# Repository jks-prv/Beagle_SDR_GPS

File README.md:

[updated 10 November 2024]

Click image for full size.

KiwiSDR
=======

> [!IMPORTANT]
> This repo is now archived.
> Look for future updates on the new repo named "KiwiSDR".

Software-defined Radio (SDR) and GPS for the BeagleBone
----------------------------------------------------------------------

An add-on board ("cape") that turns your BeagleBone into a web-accessible shortwave receiver.

### Details

* Listen live: [List](http://rx.kiwisdr.com), [Map](http://map.kiwisdr.com)
* [Online Store](https://kiwisdr.nz)
* [Project webpage](http://www.kiwisdr.com)
* [Operating information: installation, operation, FAQ](http://www.kiwisdr.com/info)
* [User Forum](http://forum.kiwisdr.com)
* Latest [source code commits](https://github.com/jks-prv/Beagle_SDR_GPS/commits/master)
* [Design review document](http://kiwisdr.com/docs/KiwiSDR/KiwiSDR.design.review.pdf)
* [KiwiSDR 1 Schematic](http://www.kiwisdr.com/docs/KiwiSDR/kiwi.schematic.pdf)
* [KiwiSDR 2 Schematic](http://www.kiwisdr.com/docs/KiwiSDR/kiwi-2.schematic.pdf)

### Description
This SDR is a bit different. It has a web interface that can be used by up to four separate listeners. Each one listening and tuning an independent frequency simultaneously. See the screenshots below.

### Components
* SDR covering the 10 kHz to 30 MHz (VLF-HF) spectrum.
* Web interface based on [OpenWebRX](https://github.com/ha7ilm/openwebrx) from András Retzler, HA7ILM.
* Integrated software-defined GPS receiver from Andrew Holme's [Homemade GPS Receiver](http://www.aholme.co.uk/GPS/Main.htm).
* LTC/Analog Devices 14-bit 65 MHz ADC.
* Xilinx/AMD Artix-7 A35 FPGA.
* Maxim/Analog Devices MAX2769B GPS front-end.
* Kiwi board works with BeagleBone Green, Black, BBAI or BBAI-64.

### Features
* Open Source.
* Browser-based interface allowing multiple simultaneous user web connections.
* Each connection tunes an independent receiver channel over the entire spectrum.
* Waterfall tunes independently of audio and includes zooming and panning.
* Multi-channel, parallel DDC design using bit-width optimized CIC filters.
* Built-in signal decoding: ALE CW DRM FAX FSK FT8 HFDL IBP NAVTEX/DSC SSTV TDoA WSPR and more.
* Good performance at VLF/LF since we personally spend time monitoring those frequencies.
* Automatic frequency calibration via received GPS timing.
* Easy hardware and software setup. Browser-based configuration interface.
* KiwiSDR 2 features:
    * Reverse proxy service enabled by default to ease network installation.
    * 0 - 31.5 dB electronic attenuator.
    * External ADC clock input.
    * Built-in self test for checking the RF path.
    * 5V input reverse polarity protection.

### Status

Give the live receivers a try at the links above. You'll need a recent version of a modern web browser that supports HTML5. The web interface works, with some problems, on mobile devices. But there is no mobile version of the interface yet.

A second generation device, the [KiwiSDR 2](https://forum.kiwisdr.com/index.php?p=/discussion/2986/kiwisdr-2-prototypes-working/p1), is now in production.

### Objectives

We wanted to design an SDR that provides certain features, at a low price point, that we felt weren't covered by current devices. The SDR must be web-accessible and simple to setup and use.
We also wanted to provide a self-contained platform for experimentation with SDR and GPS techniques. The TDoA extension is an example.

Most importantly, we wanted to see a significant number of web-enabled, wide-band SDRs deployed in diverse locations world-wide because that makes possible some really interesting applications and experiments. Over 700 Kiwis are publicly available currently.

### Operation

Users can purchase just the KiwiSDR board or a complete unit consisting of the board, BeagleBone Green (software pre-installed), enclosure, and GPS antenna (see [here](http://www.kiwisdr.com/)).
The software will try to automatically open up an incoming port through whatever Internet firewall/router may exist on the local network, but the user may have to perform this step manually. A reverse proxy service is available.

An antenna solution must be provided. An adequate power supply (e.g. 5V @ 2A) will also be required.

Four channels of audio and waterfall streamed over the Internet 24/7 requires about 30 GB per month. This is a common cap for many residential broadband plans. An automatic dynamic-DNS system is already part of the software so a web link to the SDR is immediately available with no configuration. Of course the system can be configured to only allow connections from the local network and ignore Internet connection requests.

### Web interface and built-in signal decoder screenshots:

Click images for full size.

#### Not many SDRs can show the entire 10 kHz to 30 MHz spectrum at one time.

#### Waterfall/spectrum has 15 levels of zoom (z0 - z14).
Here is z14 (2 kHz span) on the left showing the 25 Hz sweep rate of an Over the Horizon Radar (OTHR) which is very helpful with signal identification. On the right is z10 showing the full passband.

#### The Kiwi is excellent at VLF/LF reception.
Especially with the right antenna and after eliminating noise sources. When you zoom in further the labels below the spectrum clearly identify all these signals.

#### High frequency trading signal on left, CQWW RTTY DX contest on right.

#### The Kiwi has built-in decoders for various ham radio and shortwave signals.
Here is ham slow-scan television decoding.

#### Ham FT8 mode on 30 meters.
Note FT8 pileup 3 kHz below working YJ0TT Vanuatu.

#### Digital Radio Mondial (DRM), including image slideshow and Journaline text decoding.

#### Time Difference of Arrival (TDoA) signal direction finding.
Multiple Kiwis, assisted by their built-in GPS for accurate timing, can cooperate to approximately locate signals.
LF time station DCF77 77.5 kHz in Germany accurately located.

#### High Frequency Data Link (HFDL) decoding.
Aircraft to ground station (green) data exchange system. Includes message decoding and aircraft positions (blue) on a map.

#### Facimile (FAX) decoding.

#### Frequency shift keying (FSK, RTTY) decoding.

#### Other decoders:

IQ display showing the QPSK modulation of VLF station NLM4 North Dakota (25.2 kHz) as received in Kansas.

Decoding of time station WWVB (60 kHz, phase modulation) in Colorado.

When the Russian VLF Alpha navigation system is active there's a special decoder for that too.

A simple monitor for the Loran-C and under-development eLoran system. A recent West Coast USA eLoran test shown here.

[end-of-document]

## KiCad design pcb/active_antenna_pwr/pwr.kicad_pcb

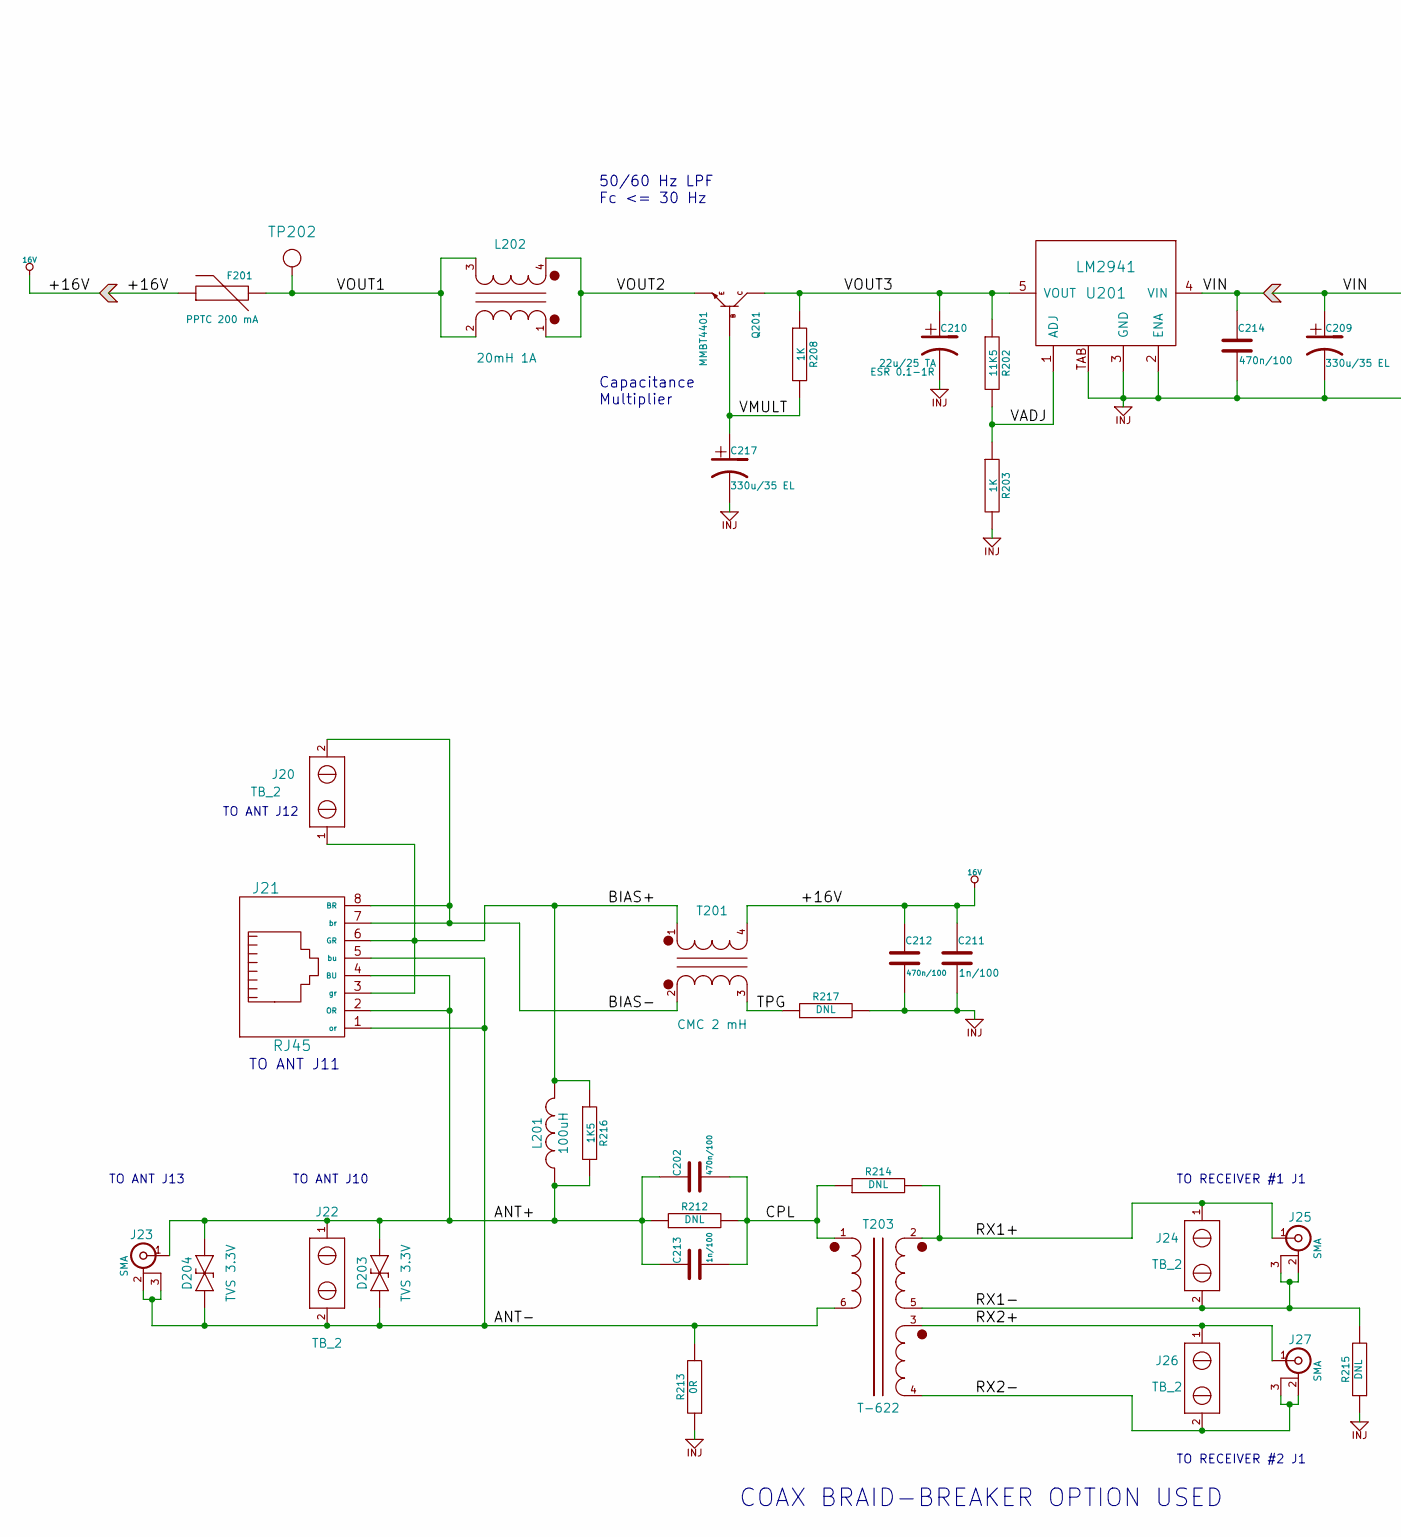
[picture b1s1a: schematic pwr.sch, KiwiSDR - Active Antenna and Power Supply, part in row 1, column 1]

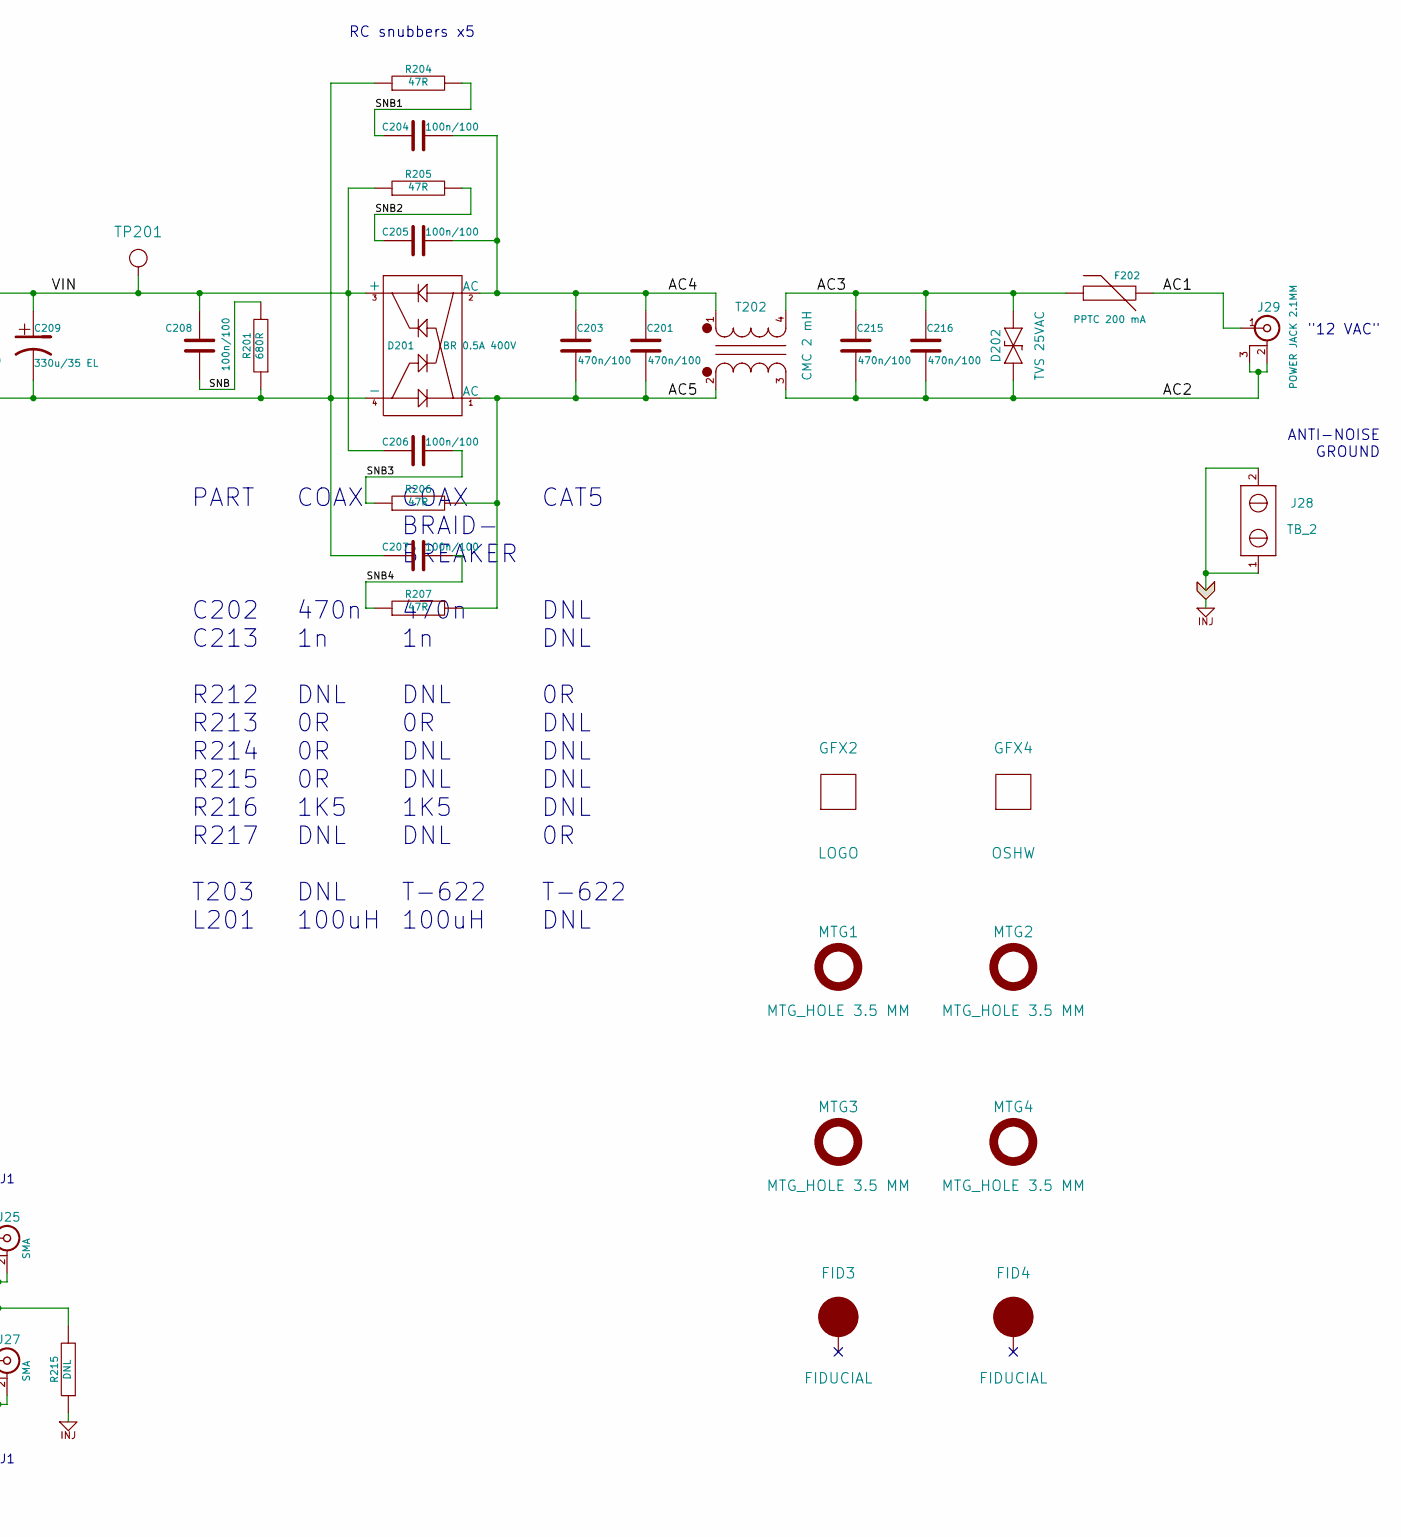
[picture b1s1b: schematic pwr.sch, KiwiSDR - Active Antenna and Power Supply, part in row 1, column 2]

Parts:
C201, C202, C203, C212, C214, C215, C216: 470n/100; kiwi-SM1206
C204, C205, C206, C207, C208: 100n/100; kiwi-SM0805
C209, C217: 330u/35 EL; kiwi-CAP_10x10
C210: 22u/25 TA; kiwi-CAP_D
C211, C213: 1n/100; kiwi-SM0805
D201: BR 0.5A 400V; kiwi-TO269_AA
D202: TVS 25VAC; kiwi-SM0805
D203, D204: TVS 3.3V; kiwi-SOD323
F201, F202: PPTC 200 mA; kiwi-SM1812
FID3, FID4: FIDUCIAL; kiwi-FIDUCIAL
GFX2: LOGO; kiwi-KIWI_10MM
GFX4: OSHW; kiwi-OSHW_6MM
J20, J22, J24, J26, J28: TB_2; kiwi-TB_2P_2_54MM
J21: RJ45; kiwi-RJ45_8
J23, J25, J27: SMA; kiwi-BNC_SMA_NO_VIP
J29: POWER JACK 2.1MM; kiwi-DC_JACK_2_1MM
L201: 100uH; kiwi-SM1812
L202: 20mH 1A; kiwi-CMC_22x22
MTG1, MTG2, MTG3, MTG4: MTG_HOLE 3.5 MM; kiwi-MTG_NPTH_3_5MM
Q201: MMBT4401; kiwi-SOT23_BCE
R201: 680R; kiwi-SM0805
R202: 11K5; kiwi-SM0805
R203, R208: 1K; kiwi-SM0805
R204, R205, R206, R207: 47R; kiwi-SM0805
R212, R214, R215, R217: DNL; kiwi-SM0805
R213: 0R; kiwi-SM0805
R216: 1K5; kiwi-SM0805
T201, T202: CMC 2 mH; kiwi-CMC
T203: T-622; kiwi-MCL_KK81
TP201, TP202: TEST_POINT; kiwi-TP_1250
U201: LM2941; kiwi-TO263

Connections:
/AC1: F202.2, J29.1 (In)
/AC2: C215.2, C216.2, D202.1, J29.2 (gnd), J29.3 (gnd), T202.3
/AC3: C215.1, C216.1, D202.2, F202.1, T202.4
/AC4: C201.1, C203.1, C204.2, C205.2, D201.2 (AC), T202.1
/AC5: C201.2, C203.2, D201.1 (AC), R206.2, R207.2, T202.2
/ANT+: C202.1, C213.1, D203.2, D204.2, J21.2 (OR), J21.4 (BU), J22.1, J23.1 (In), L201.1, R212.1, R216.2
/ANT-: D203.1, D204.1, J21.1 (or), J21.5 (bu), J22.2, J23.2 (gnd), J23.3 (gnd), R213.2, T203.6
/BIAS+: J20.1, J21.3 (gr), J21.6 (GR), L201.2, R216.1, T201.1
/BIAS-: J20.2, J21.7 (br), J21.8 (BR), T201.2
/CPL: C202.2, C213.2, R212.2, R214.1, T203.1
/RX1+: J24.1, J25.1 (In), R214.2, T203.2
/RX1-: J24.2, J25.2 (gnd), J25.3 (gnd), R215.2, T203.5
/RX2+: J26.1, J27.1 (In), T203.3
/RX2-: J26.2, J27.2 (gnd), J27.3 (gnd), T203.4
/SNB: C208.2, R201.2
/SNB1: C204.1, R204.2
/SNB2: C205.1, R205.2
/SNB3: C206.2, R206.1
/SNB4: C207.2, R207.1
/TPG: R217.1, T201.3
/VADJ: R202.2, R203.1, U201.1 (ADJ)
/VMULT: C217.1, Q201.B, R208.2
/VOUT1: F201.2, L202.2, L202.3, TP202.1
/VOUT2: L202.1, L202.4, Q201.E
/VOUT3: C210.1, Q201.C, R202.1, R208.1, U201.5 (VOUT)

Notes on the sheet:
"12 VAC"
RC snubbers x5
PART C202 C213 R212 R213 R214 R215 R216 R217 T203 L201
COAX BRAID- BREAKER 470n 1n DNL 0R DNL DNL 1K5 DNL T-622 100uH
CAT5 DNL DNL 0R DNL DNL DNL DNL 0R T-622 DNL
TO ANT J12
TO ANT J11
TO RECEIVER #1 J1
TO ANT J10
50/60 Hz LPF Fc <= 30 Hz
Capacitance Multiplier
ANTI-NOISE GROUND
COAX 470n 1n DNL 0R 0R 0R 1K5 DNL DNL 100uH
TO ANT J13
TO RECEIVER #2 J1
COAX BRAID-BREAKER OPTION USED

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
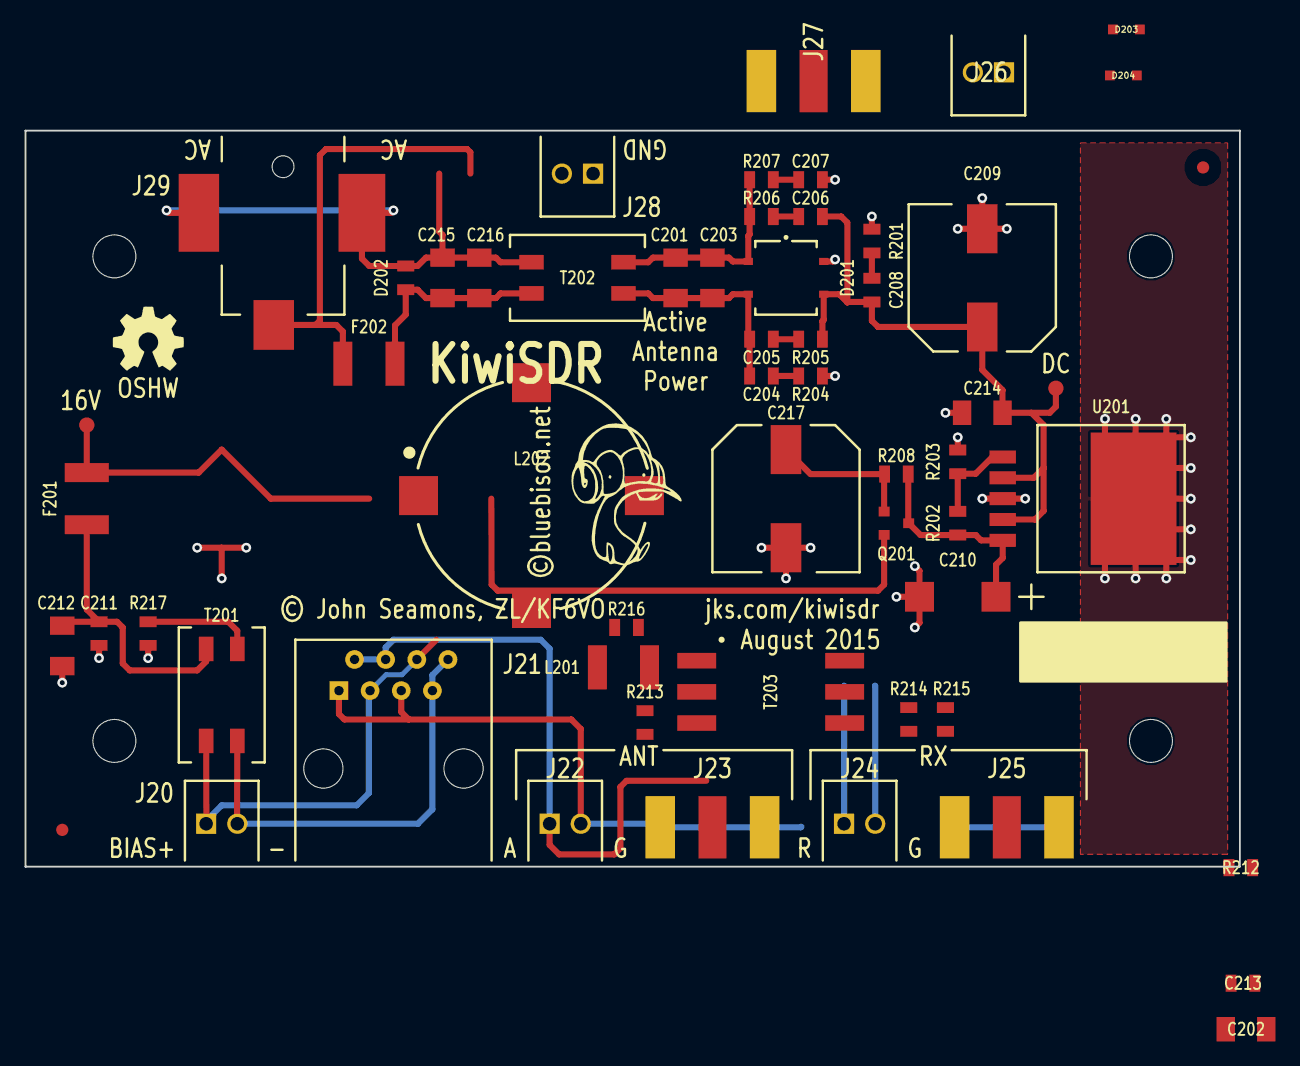
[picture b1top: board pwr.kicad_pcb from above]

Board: 2 copper layers, 99.0 x 60.0 mm, 64 parts (0 on the bottom side), 29 nets.

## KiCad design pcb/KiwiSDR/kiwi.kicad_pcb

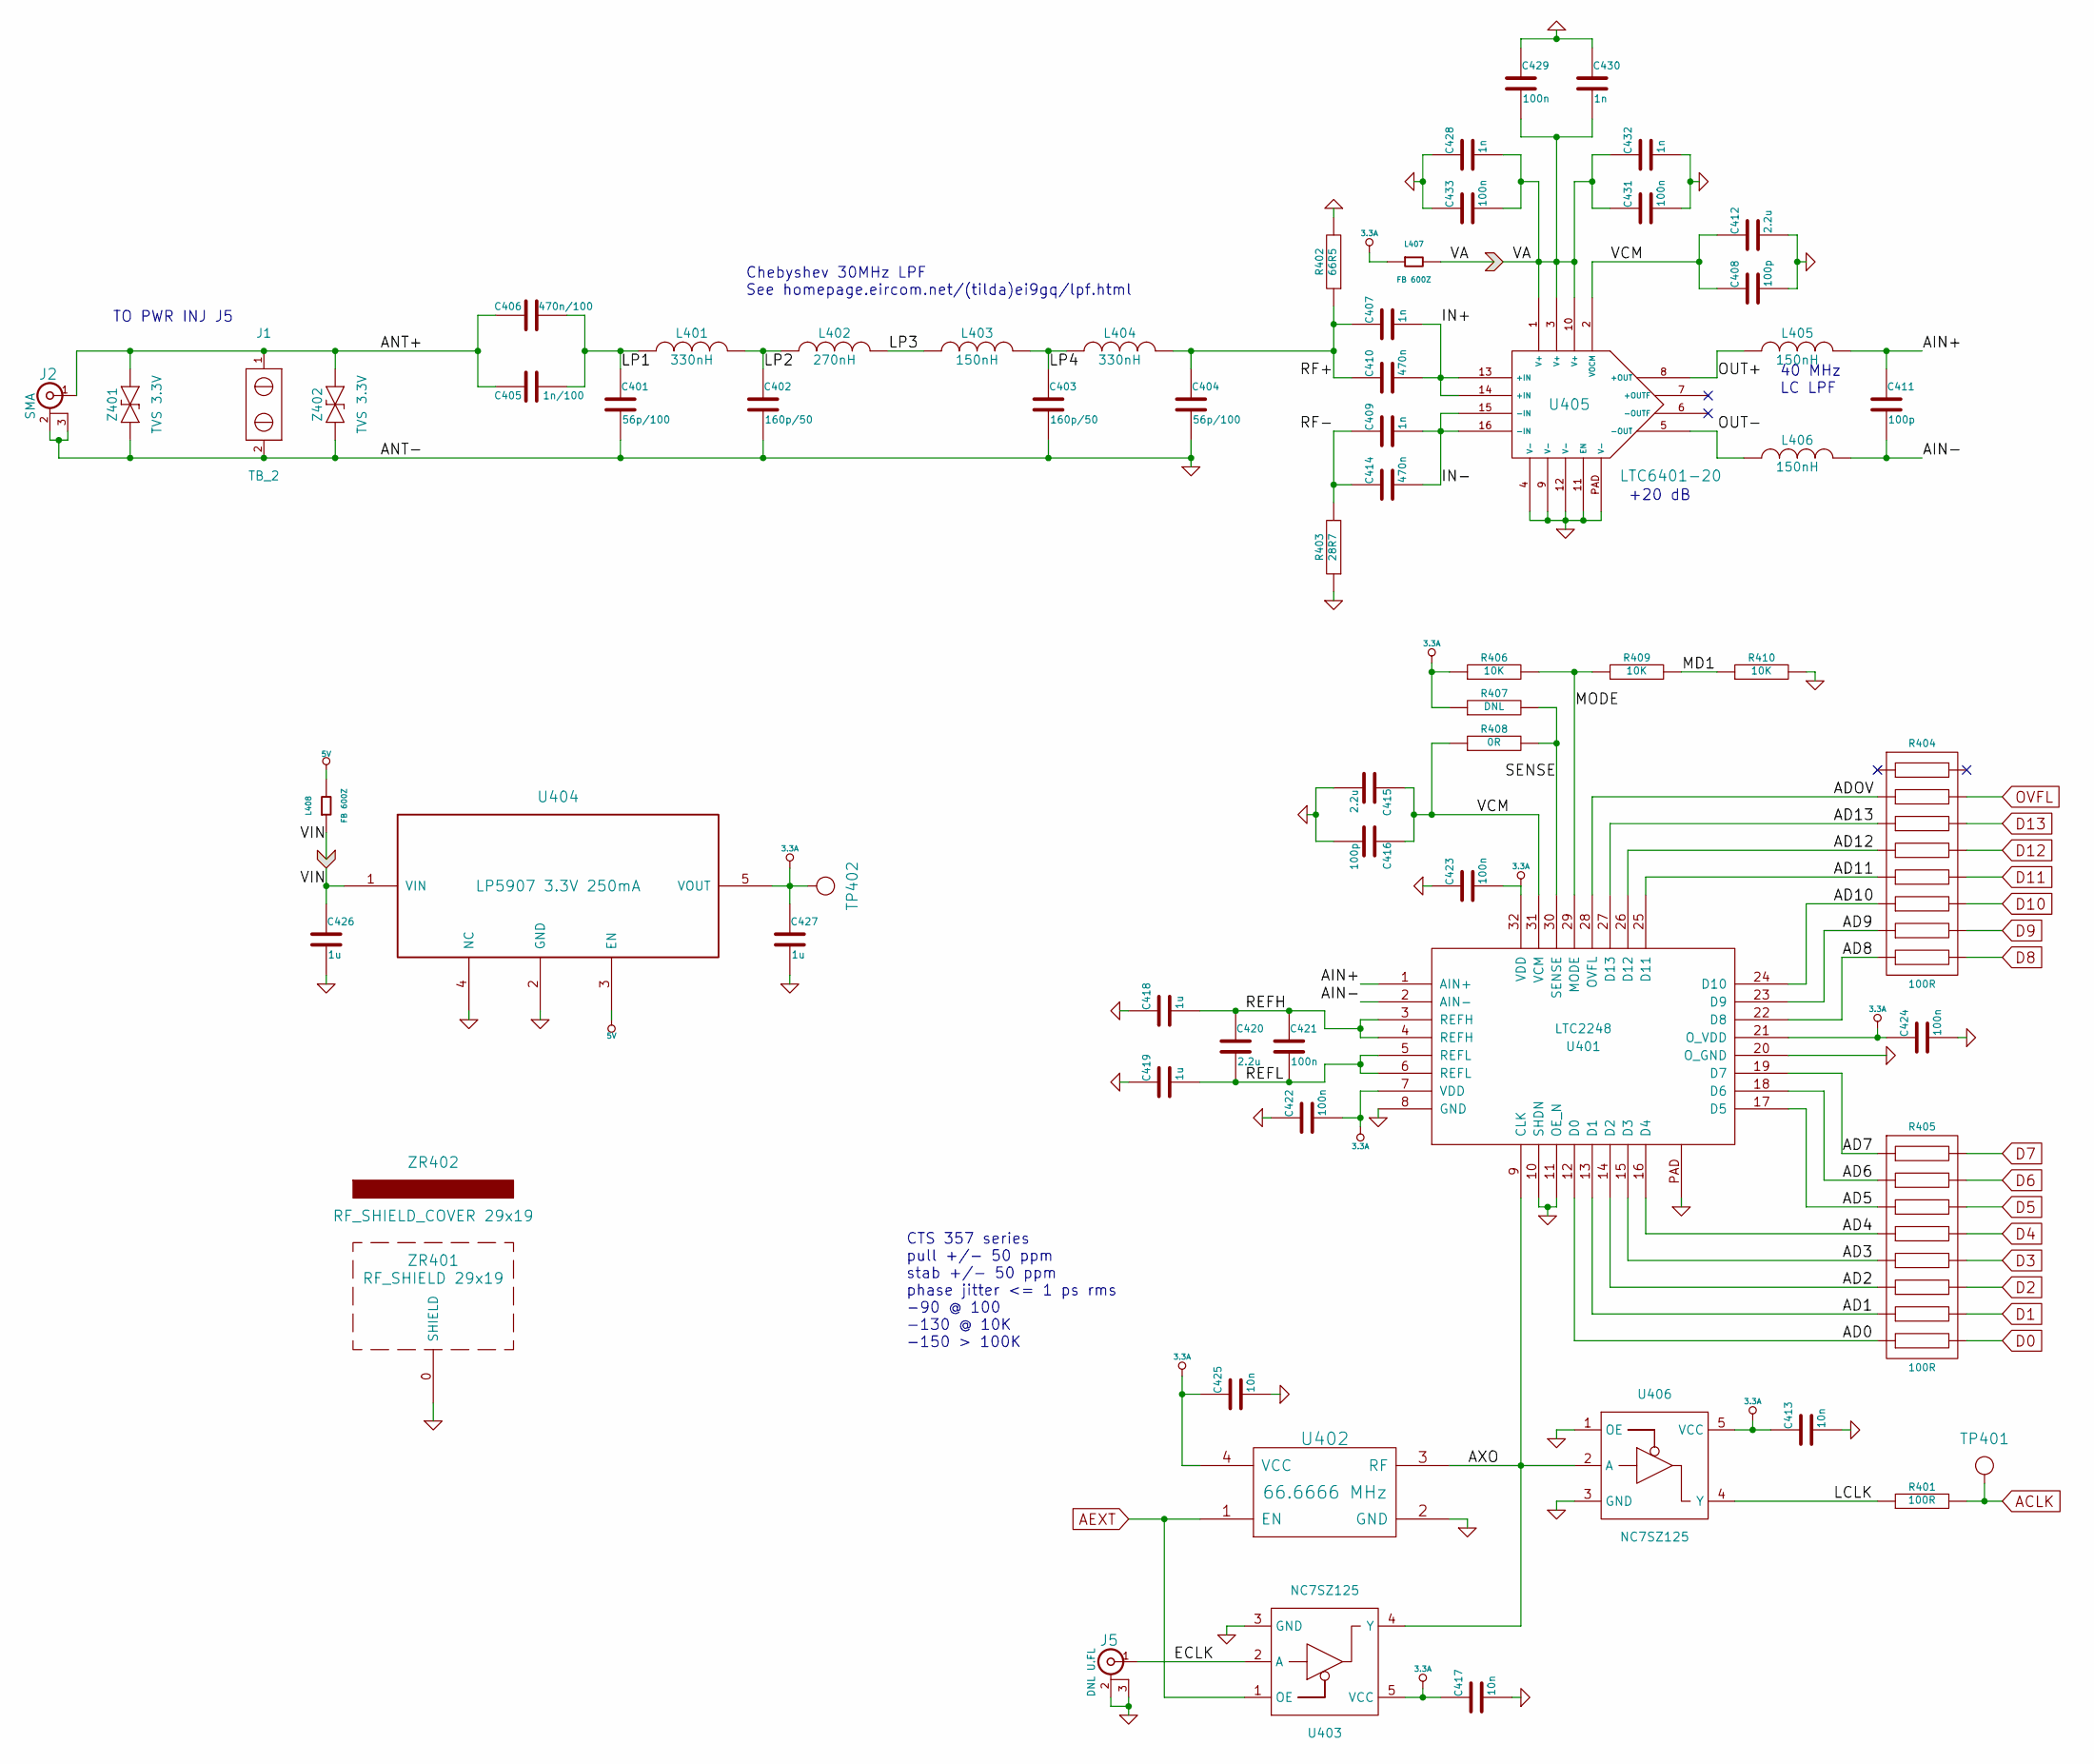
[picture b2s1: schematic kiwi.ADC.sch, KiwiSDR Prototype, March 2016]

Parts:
C401, C404: 56p/100; kiwi-SM0402
C402, C403: 160p/50; kiwi-SM0402
C405: 1n/100; kiwi-SM0805
C406: 470n/100; kiwi-SM1206
C407, C409, C428, C430, C432: 1n; kiwi-SM0402
C408, C411, C416: 100p; kiwi-SM0402
C410, C414: 470n; kiwi-SM0402
C412, C415, C420: 2.2u; kiwi-SM0402
C413, C417, C425: 10n; kiwi-SM0402
C418, C419, C426, C427: 1u; kiwi-SM0402
C421, C422, C423, C424, C429, C431, C433: 100n; kiwi-SM0402
J1: TB_2; kiwi-TB_2P_2_54MM
J2: SMA; kiwi-SMA_OPL_EM
J5: DNL U.FL; kiwi-U.FL
L401, L404: 330nH; kiwi-SM0402
L402: 270nH; kiwi-SM0402
L403, L405, L406: 150nH; kiwi-SM0402
L407, L408: FB 600Z; kiwi-SM0402
R401: 100R; kiwi-SM0402
R402: 66R5; kiwi-SM0402
R403: 28R7; kiwi-SM0402
R404, R405: 100R; kiwi-RNET_CAY16_J8
R406, R409, R410: 10K; kiwi-SM0402
R407: DNL; kiwi-SM0402
R408: 0R; kiwi-SM0402
TP401: TEST_POINT; kiwi-TP_600
TP402: TEST_POINT; kiwi-TP_VIA_600
U401: LTC2248; kiwi-QFN32
U402: 66.6666 MHz; kiwi-XO
U403, U406: NC7SZ125; kiwi-SC70_5
U404: LP5907 3.3V 250mA; kiwi-SOT23_5
U405: LTC6401-20; kiwi-QFN16
Z401, Z402: TVS 3.3V; kiwi-SOD323
ZR401: RF_SHIELD 29x19; kiwi-RF_SHIELD_29x19
ZR402: RF_SHIELD_COVER 29x19; kiwi-RF_SHIELD_COVER

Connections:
3.3A: C413.1, C417.1, C422.2, C423.2, C424.1, C425.1, C427.1, L407.1, R406.1, R407.1, TP402.1, U401.7 (VDD), U401.21 (O_VDD), U401.32 (VDD), U402.4 (VCC), U403.5 (VCC), U404.5 (VOUT), U406.5 (VCC)
/ADC/AD0: R405.15, U401.12 (D0)
/ADC/AD1: R405.13, U401.13 (D1)
/ADC/AD2: R405.11, U401.14 (D2)
/ADC/AD3: R405.9, U401.15 (D3)
/ADC/AD4: R405.7, U401.16 (D4)
/ADC/AD5: R405.5, U401.17 (D5)
/ADC/AD6: R405.3, U401.18 (D6)
/ADC/AD7: R405.1, U401.19 (D7)
/ADC/AD8: R404.15, U401.22 (D8)
/ADC/AD9: R404.13, U401.23 (D9)
/ADC/AD10: R404.11, U401.24 (D10)
/ADC/AD11: R404.9, U401.25 (D11)
/ADC/AD12: R404.7, U401.26 (D12)
/ADC/AD13: R404.5, U401.27 (D13)
/ADC/ADOV: R404.3, U401.28 (OVFL)
/ADC/AIN+: C411.1, L405.2, U401.1 (AIN+)
/ADC/AIN-: C411.2, L406.2, U401.2 (AIN-)
/ADC/ANT+: C405.1, C406.1, J1.1, J2.1 (In), Z401.2, Z402.2
/ADC/AXO: U401.9 (CLK), U402.3 (RF), U403.4 (Y), U406.2 (A)
/ADC/ECLK: J5.1 (In), U403.2 (A)
/ADC/IN+: C407.2, C410.2, U405.13 (+IN), U405.14 (+IN)
/ADC/IN-: C409.2, C414.2, U405.15 (-IN), U405.16 (-IN)
/ADC/LCLK: R401.1, U406.4 (Y)
/ADC/LP1: C401.1, C405.2, C406.2, L401.1
/ADC/LP2: C402.1, L401.2, L402.1
/ADC/LP3: L402.2, L403.1
/ADC/LP4: C403.1, L403.2, L404.1
/ADC/MD1: R409.2, R410.1
/ADC/MODE: R406.2, R409.1, U401.29 (MODE)
/ADC/OUT+: L405.1, U405.8 (+OUT)
/ADC/OUT-: L406.1, U405.5 (-OUT)
/ADC/REFH: C418.2, C420.1, C421.1, U401.3 (REFH), U401.4 (REFH)
/ADC/REFL: C419.2, C420.2, C421.2, U401.5 (REFL), U401.6 (REFL)
/ADC/RF+: C404.1, C407.1, C410.1, L404.2, R402.1
/ADC/RF-: C409.1, C414.1, R403.2
/ADC/SENSE: R407.2, R408.2, U401.30 (SENSE)
/ADC/VCM: C408.1, C412.1, C415.1, C416.1, R408.1, U401.31 (VCM), U405.2 (VOCM)
ACLK: R401.2, TP401.1; also elsewhere on the board
AEXT: U402.1 (EN), U403.1 (OE); also elsewhere on the board
D0: R405.16; also elsewhere on the board
D1: R405.14; also elsewhere on the board
D2: R405.12; also elsewhere on the board
D3: R405.10; also elsewhere on the board
D4: R405.8; also elsewhere on the board
D5: R405.6; also elsewhere on the board
D6: R405.4; also elsewhere on the board
D7: R405.2; also elsewhere on the board
D8: R404.16; also elsewhere on the board
D9: R404.14; also elsewhere on the board
D10: R404.12; also elsewhere on the board
D11: R404.10; also elsewhere on the board
D12: R404.8; also elsewhere on the board
D13: R404.6; also elsewhere on the board
OVFL: R404.4; also elsewhere on the board

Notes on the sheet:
CTS 357 series pull +/- 50 ppm stab +/- 50 ppm phase jitter <= 1 ps rms -90 @ 100 -130 @ 10K -150 > 100K
Chebyshev 30MHz LPF See homepage.eircom.net/(tilda)ei9gq/lpf.html
40 MHz LC LPF
+20 dB
TO PWR INJ J5

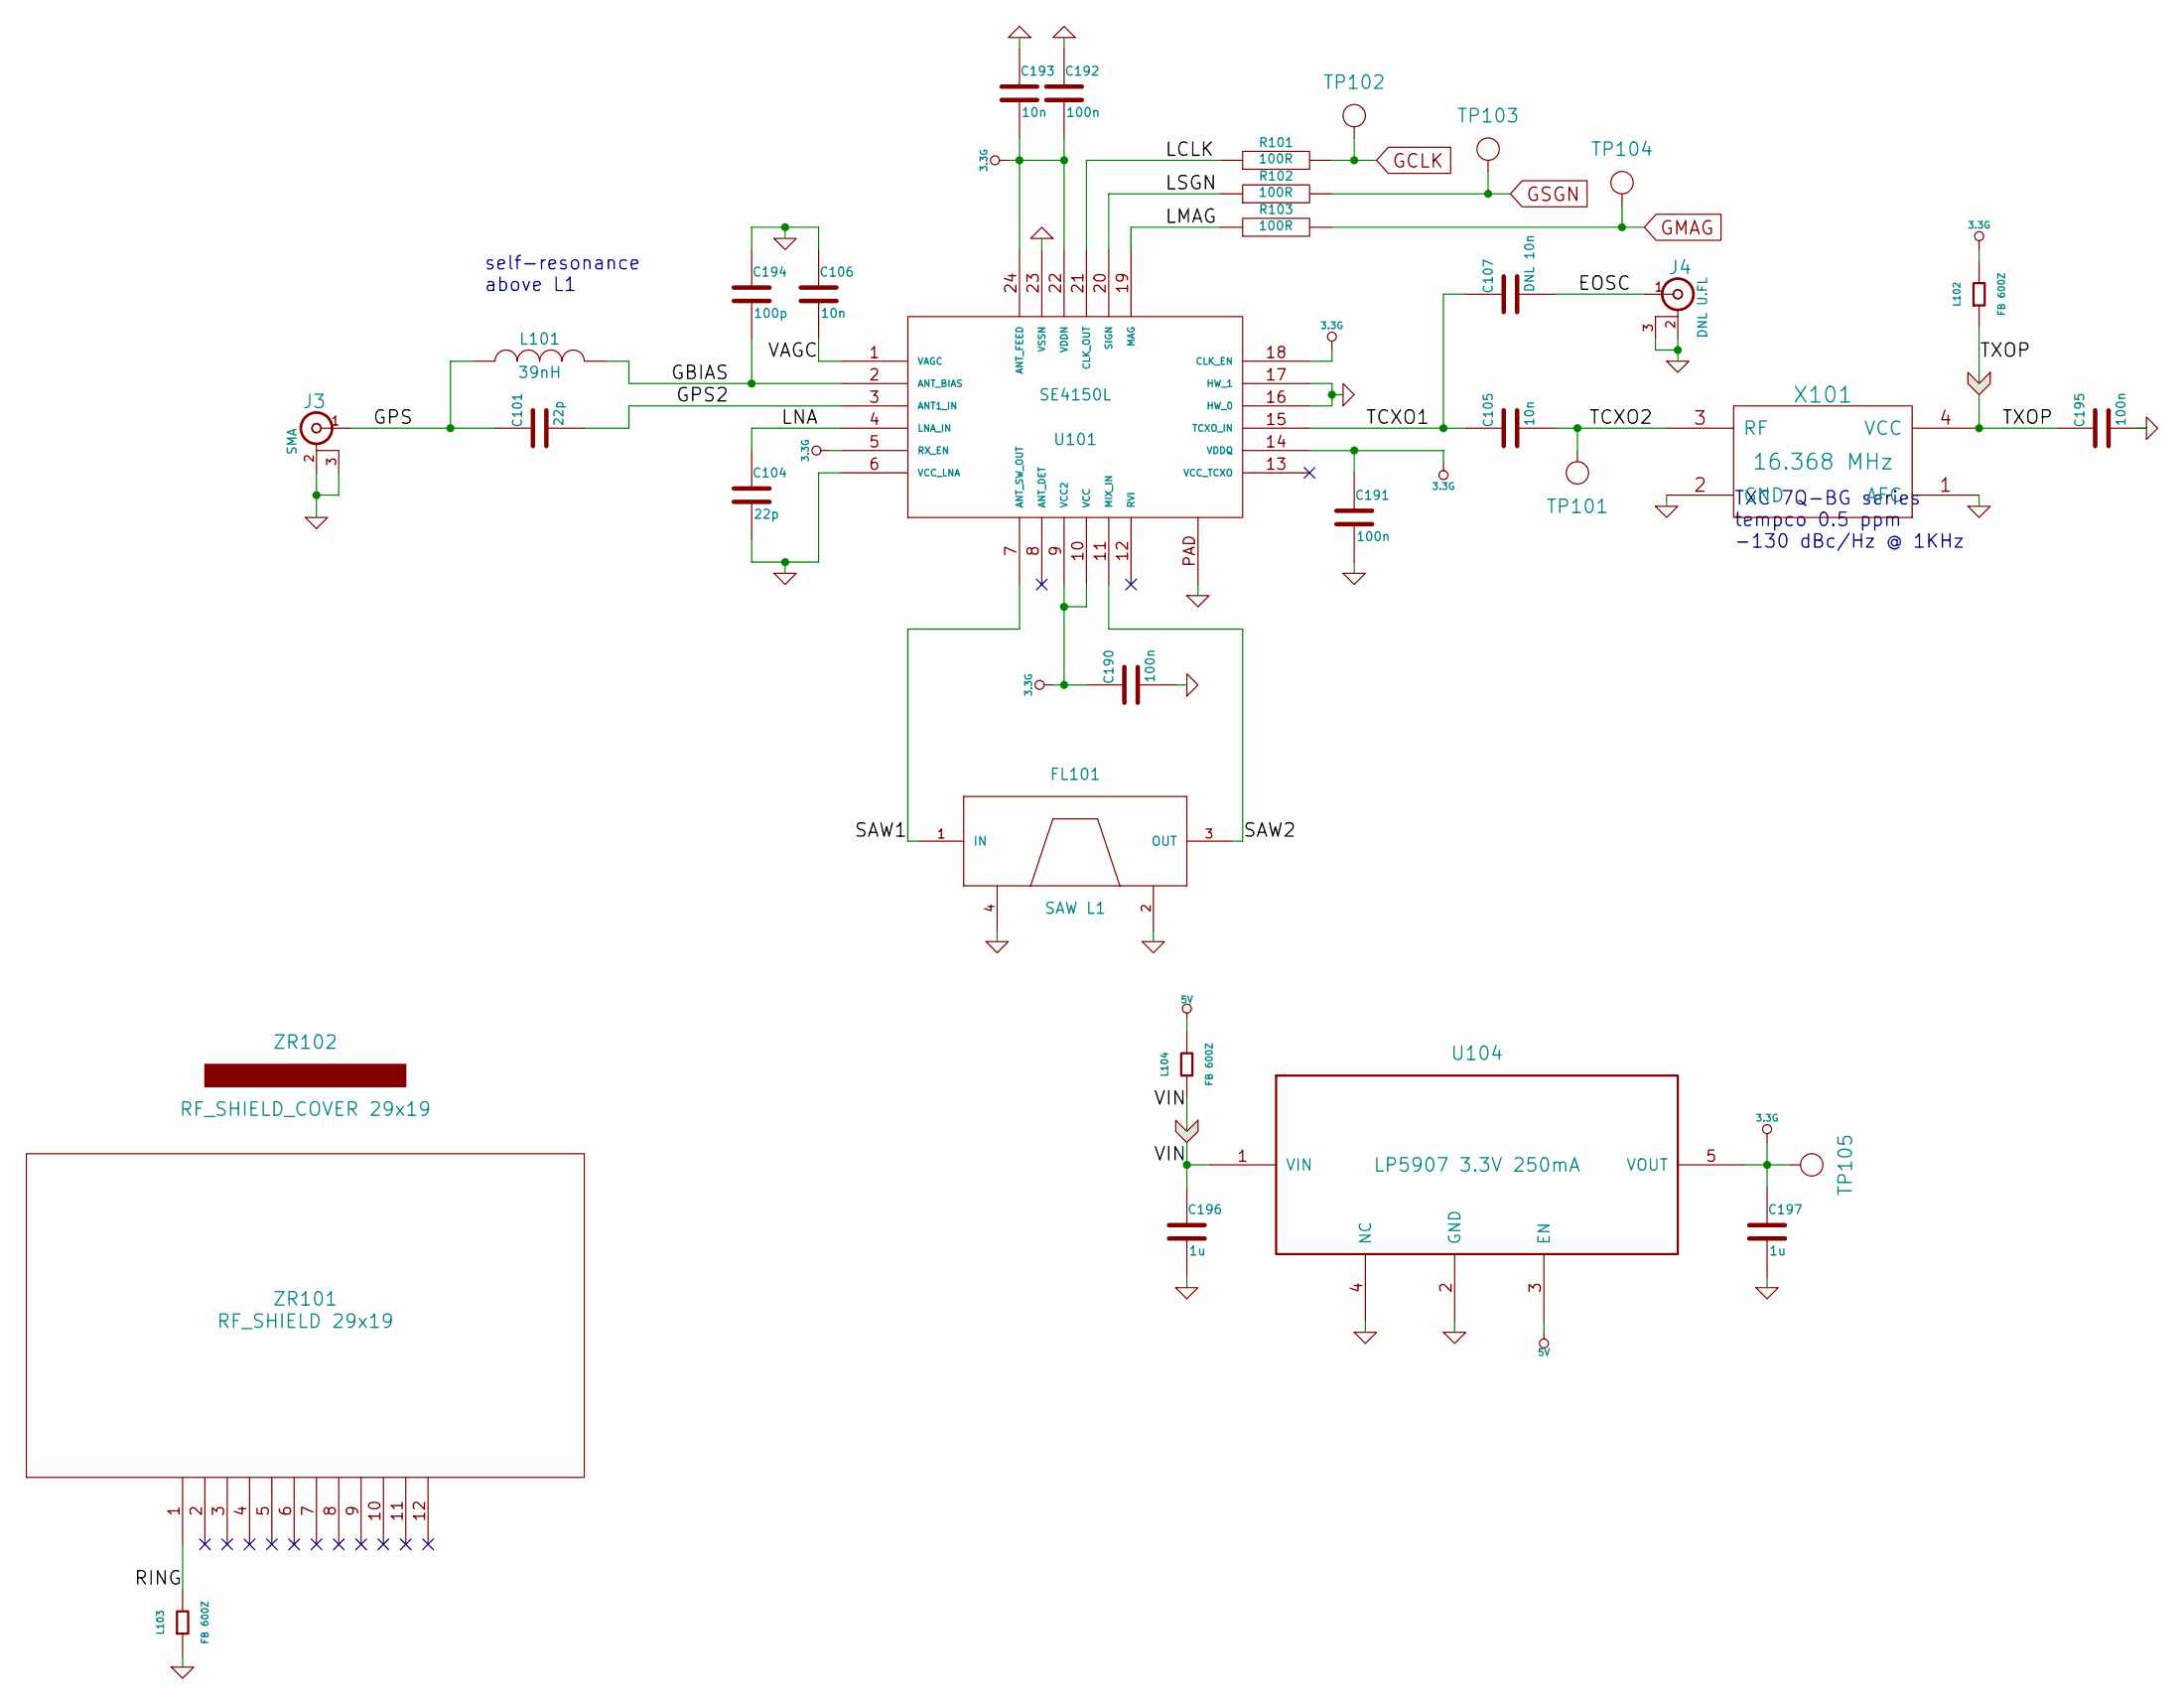
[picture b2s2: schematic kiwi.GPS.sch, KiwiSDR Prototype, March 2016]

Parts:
C101, C104: 22p; kiwi-SM0402
C105, C106, C193: 10n; kiwi-SM0402
C107: DNL 10n; kiwi-SM0402
C190, C191, C192, C195: 100n; kiwi-SM0402
C194: 100p; kiwi-SM0402
C196, C197: 1u; kiwi-SM0402
FL101: SAW L1; kiwi-SAW
J3: SMA; kiwi-SMA_OPL_EM
J4: DNL U.FL; kiwi-U.FL
L101: 39nH; kiwi-SM0402
L102, L103, L104: FB 600Z; kiwi-SM0402
R101, R102, R103: 100R; kiwi-SM0402
TP101, TP105: TEST_POINT; kiwi-TP_600
TP102, TP103, TP104: TEST_POINT; kiwi-TP_VIA_1250
U101: SE4150L; kiwi-QFN24
U104: LP5907 3.3V 250mA; kiwi-SOT23_5
X101: 16.368 MHz; kiwi-TCXO
ZR101: RF_SHIELD 29x19; kiwi-RF_SHIELD_29x19_16P
ZR102: RF_SHIELD_COVER 29x19; kiwi-RF_SHIELD_COVER

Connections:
3.3G: C190.1, C191.1, C192.2, C193.2, C197.1, L102.2, TP105.1, U101.5 (RX_EN), U101.9 (VCC2), U101.10 (VCC), U101.14 (VDDQ), U101.18 (CLK_EN), U101.22 (VDDN), U101.24 (ANT_FEED), U104.5 (VOUT)
/GPS/EOSC: C107.2, J4.1 (In)
/GPS/GBIAS: C194.2, L101.2, U101.2 (ANT_BIAS)
/GPS/GPS: C101.1, J3.1 (In), L101.1
/GPS/GPS2: C101.2, U101.3 (ANT1_IN)
/GPS/LCLK: R101.1, U101.21 (CLK_OUT)
/GPS/LMAG: R103.1, U101.19 (MAG)
/GPS/LNA: C104.1, U101.4 (LNA_IN)
/GPS/LSGN: R102.1, U101.20 (SIGN)
/GPS/RING: L103.2, ZR101.1
/GPS/SAW1: FL101.1 (IN), U101.7 (ANT_SW_OUT)
/GPS/SAW2: FL101.3 (OUT), U101.11 (MIX_IN)
/GPS/TCXO1: C105.1, C107.1, U101.15 (TCXO_IN)
/GPS/TCXO2: C105.2, TP101.1, X101.3 (RF)
/GPS/VAGC: C106.2, U101.1 (VAGC)
GCLK: R101.2, TP102.1; also elsewhere on the board
GMAG: R103.2, TP104.1; also elsewhere on the board
GSGN: R102.2, TP103.1; also elsewhere on the board

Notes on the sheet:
self-resonance above L1
TXC 7Q-BG series tempco 0.5 ppm -130 dBc/Hz @ 1KHz

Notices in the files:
pcb/KiwiSDR/kiwi.kicad_pcb:
© John Seamons
©bluebison.net
pcb/active_antenna/ant.kicad_pcb:
©Point Reyes Ventures, LLC
©Sonoran Radio Research
pcb/active_antenna_pwr/pwr.kicad_pcb:
© John Seamons, ZL/KF6VO
